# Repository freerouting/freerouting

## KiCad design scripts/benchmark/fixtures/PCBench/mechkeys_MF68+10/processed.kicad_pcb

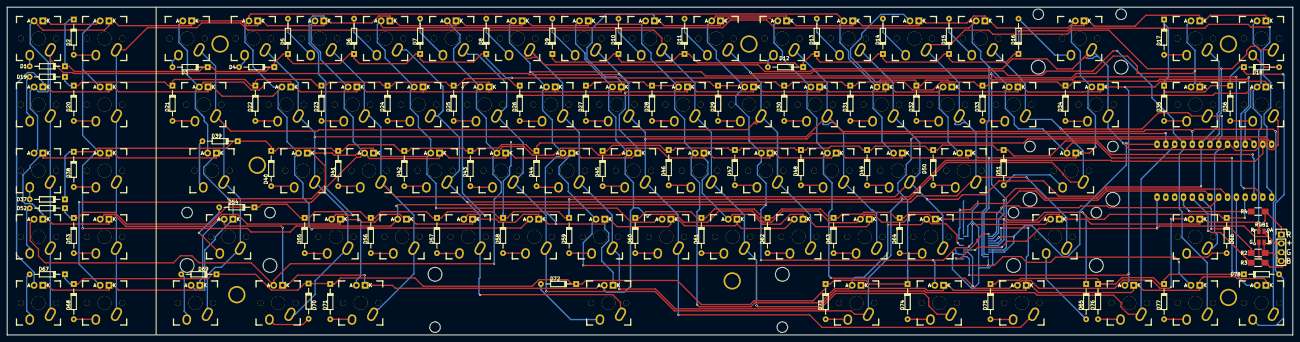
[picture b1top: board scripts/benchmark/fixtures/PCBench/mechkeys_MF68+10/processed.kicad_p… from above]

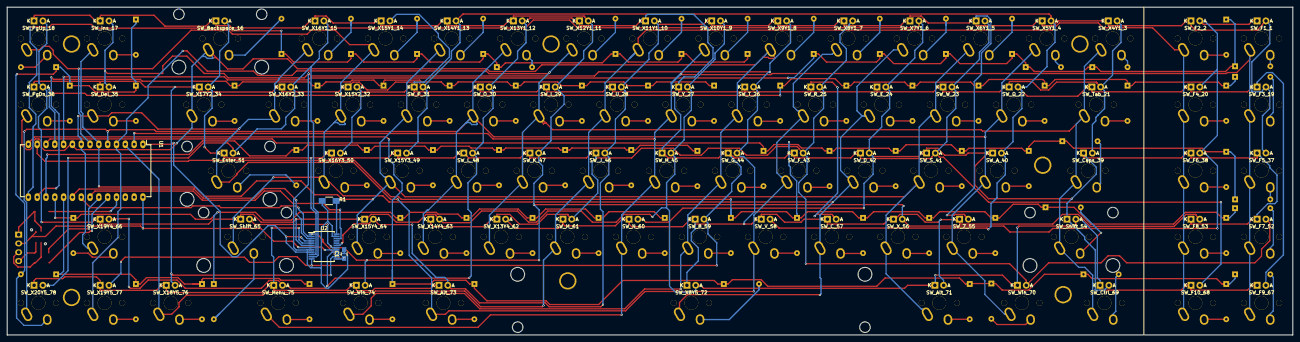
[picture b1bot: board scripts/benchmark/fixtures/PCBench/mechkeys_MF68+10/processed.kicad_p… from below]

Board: 2 copper layers, 370.5 x 94.4 mm, 170 parts (4 on the bottom side), 119 nets.

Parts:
C1: 1µF; C_0805_HandSoldering
CHERRY: MX; CHERRY_PCB_200H_STABILIZER
CHERRY_2, CHERRY_4: MX; CHERRY_PCB_225H_STABILIZER
CHERRY_3: MX; CHERRY_PCB_625H_STABILIZER
CHERRY_5: MX; CHERRY_PCB_275H_STABILIZER
D1, D2, D3, D4, D5, D6, D7, D8, D9, D10, D11, D12, D13, D14, D15, D16, D17, D18, D19, D20, D21, D22, D23, D24, D25, D26, D27, D28, D29, D30, D31, D32, D33, D34, D35, D36, D37, D38, D39, D40, D41, D42, D43, D44, D45, D46, D47, D48, D49, D50, D51, D52, D53, D54, D55, D56, D57, D58, D59, D60, D61, D62, D63, D64, D65, D66, D67, D68, D69, D70, D71, D72, D73, D74, D75, D76, D77, D78: D; Diode_DO-35_SOD27_Horizontal_RM10
GND: MountingHole_5.3mm_M5
R1: 39kΩ; R_1206_HandSoldering
R2: 150Ω; R_1206_HandSoldering
R3, R4: 120Ω; R_1206_HandSoldering
RGB1: Led_RGB_CA; SMP4-RGB
SW_A_40: MX_LED; MXALPS
SW_Alt_71, SW_Alt_73: MX_LED; MXALPS
SW_B_59: MX_LED; MXALPS
SW_Backspace_16: MX_LED; MXALPS
SW_C_57: MX_LED; MXALPS
SW_Caps_39: MX_LED; MXALPS
SW_Ctrl_69: MX_LED; MXALPS
SW_D_42: MX_LED; MXALPS
SW_Del_35: MX_LED; MXALPS
SW_E_24: MX_LED; MXALPS
SW_Enter_51: MX_LED; MXALPS
SW_F1_1, SW_F2_2, SW_F3_19, SW_F4_20, SW_F5_37, SW_F6_38, SW_F7_52, SW_F8_53, SW_F9_67, SW_F10_68: MX_LED; MXALPS
SW_F_43: MX_LED; MXALPS
SW_G_44: MX_LED; MXALPS
SW_H_45: MX_LED; MXALPS
SW_I_29: MX_LED; MXALPS
SW_Ins_17: MX_LED; MXALPS
SW_J_46: MX_LED; MXALPS
SW_K_47: MX_LED; MXALPS
SW_L_48: MX_LED; MXALPS
SW_M_61: MX_LED; MXALPS
SW_Menu_75: MX_LED; MXALPS
SW_N_60: MX_LED; MXALPS
SW_O_30: MX_LED; MXALPS
SW_P_31: MX_LED; MXALPS
SW_PgDn_36: MX_LED; MXALPS
SW_PgUp_18: MX_LED; MXALPS
SW_Q_22: MX_LED; MXALPS
SW_R_25: MX_LED; MXALPS
SW_S_41: MX_LED; MXALPS
SW_Shift_54, SW_Shift_65: MX_LED; MXALPS
SW_T_26: MX_LED; MXALPS
SW_Tab_21: MX_LED; MXALPS
SW_U_28: MX_LED; MXALPS
SW_V_58: MX_LED; MXALPS
SW_W_23: MX_LED; MXALPS
SW_Win_70, SW_Win_74: MX_LED; MXALPS
SW_X4Y1_3, SW_X5Y1_4, SW_X6Y1_5, SW_X7Y1_6, SW_X8Y1_7, SW_X8Y5_72, SW_X9Y1_8, SW_X10Y1_9, SW_X11Y1_10, SW_X12Y1_11, SW_X13Y1_12, SW_X13Y4_62, SW_X14Y1_13, SW_X14Y4_63, SW_X15Y1_14, SW_X15Y2_32, SW_X15Y3_49, SW_X15Y4_64, SW_X16Y1_15, SW_X16Y2_33, SW_X16Y3_50, SW_X17Y2_34, SW_X18Y5_76, SW_X19Y4_66, SW_X19Y5_77, SW_X20Y5_78: MX_LED; MXALPS
SW_X_56: MX_LED; MXALPS
SW_Y_27: MX_LED; MXALPS
SW_Z_55: MX_LED; MXALPS
U1: Teensy_3.2; Teensy3.2
U2: AN32183A; SSOP-24_5.3x8.2mm_Pitch0.65mm

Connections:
+5V: RGB1.1, U1.Vin, U2.7, U2.17
C1: SW_F1_1.SW1, SW_F3_19.SW1, SW_F5_37.SW1, SW_F7_52.SW1, SW_F9_67.SW1, SW_H_45.SW1, SW_Menu_75.SW1, SW_N_60.SW1, SW_X10Y1_9.SW1, SW_Y_27.SW1, U1.0
C2: SW_F2_2.SW1, SW_F4_20.SW1, SW_F6_38.SW1, SW_F8_53.SW1, SW_F10_68.SW1, SW_J_46.SW1, SW_M_61.SW1, SW_U_28.SW1, SW_X11Y1_10.SW1, SW_X18Y5_76.SW1, U1.1
C3: SW_Caps_39.SW1, SW_Ctrl_69.SW1, SW_I_29.SW1, SW_K_47.SW1, SW_Shift_54.SW1, SW_Tab_21.SW1, SW_X4Y1_3.SW1, SW_X12Y1_11.SW1, SW_X13Y4_62.SW1, SW_X19Y5_77.SW1, U1.2
C4: SW_A_40.SW1, SW_L_48.SW1, SW_O_30.SW1, SW_Q_22.SW1, SW_Win_70.SW1, SW_X5Y1_4.SW1, SW_X13Y1_12.SW1, SW_X14Y4_63.SW1, SW_X20Y5_78.SW1, SW_Z_55.SW1, U1.3
C5: SW_Alt_71.SW1, SW_Ins_17.SW1, SW_P_31.SW1, SW_S_41.SW1, SW_W_23.SW1, SW_X6Y1_5.SW1, SW_X14Y1_13.SW1, SW_X15Y3_49.SW1, SW_X15Y4_64.SW1, SW_X_56.SW1, U1.4
C6: SW_C_57.SW1, SW_D_42.SW1, SW_E_24.SW1, SW_PgUp_18.SW1, SW_Shift_65.SW1, SW_X7Y1_6.SW1, SW_X8Y5_72.SW1, SW_X15Y1_14.SW1, SW_X15Y2_32.SW1, SW_X16Y3_50.SW1, U1.5
C7: SW_Alt_73.SW1, SW_Del_35.SW1, SW_Enter_51.SW1, SW_F_43.SW1, SW_R_25.SW1, SW_V_58.SW1, SW_X8Y1_7.SW1, SW_X16Y1_15.SW1, SW_X16Y2_33.SW1, SW_X19Y4_66.SW1, U1.6
C8: SW_B_59.SW1, SW_Backspace_16.SW1, SW_G_44.SW1, SW_PgDn_36.SW1, SW_T_26.SW1, SW_Win_74.SW1, SW_X9Y1_8.SW1, SW_X17Y2_34.SW1, U1.7
GND: C1.2, R1.2, U1.GND0, U2.4, U2.9, U2.15, U2.23
NSRT: U1.20, U2.22
unnamed: C1.1, U2.1, U2.13
unnamed: D1.2, SW_F1_1.SW2
unnamed: D2.2, SW_F2_2.SW2
unnamed: D3.2, SW_X4Y1_3.SW2
unnamed: D4.2, SW_X5Y1_4.SW2
unnamed: D5.2, SW_X6Y1_5.SW2
unnamed: D6.2, SW_X7Y1_6.SW2
unnamed: D7.2, SW_X8Y1_7.SW2
unnamed: D8.2, SW_X9Y1_8.SW2
unnamed: D9.2, SW_X10Y1_9.SW2
unnamed: D10.2, SW_X11Y1_10.SW2
unnamed: D11.2, SW_X12Y1_11.SW2
unnamed: D12.2, SW_X13Y1_12.SW2
unnamed: D13.2, SW_X14Y1_13.SW2
unnamed: D14.2, SW_X15Y1_14.SW2
unnamed: D15.2, SW_X16Y1_15.SW2
unnamed: D16.2, SW_Backspace_16.SW2
unnamed: D17.1, D18.1, D35.1, D36.1, D78.2, SW_X20Y5_78.SW2
unnamed: D17.2, SW_Ins_17.SW2
unnamed: D18.2, SW_PgUp_18.SW2
unnamed: D19.2, SW_F3_19.SW2
unnamed: D20.2, SW_F4_20.SW2
unnamed: D21.2, SW_Tab_21.SW2
unnamed: D22.2, SW_Q_22.SW2
unnamed: D23.2, SW_W_23.SW2
unnamed: D24.2, SW_E_24.SW2
unnamed: D25.2, SW_R_25.SW2
unnamed: D26.2, SW_T_26.SW2
unnamed: D27.2, SW_Y_27.SW2
unnamed: D28.2, SW_U_28.SW2
unnamed: D29.2, SW_I_29.SW2
unnamed: D30.2, SW_O_30.SW2
unnamed: D31.2, SW_P_31.SW2
unnamed: D32.2, SW_X15Y2_32.SW2
unnamed: D33.2, SW_X16Y2_33.SW2
unnamed: D34.2, SW_X17Y2_34.SW2
unnamed: D35.2, SW_Del_35.SW2
unnamed: D36.2, SW_PgDn_36.SW2
unnamed: D37.2, SW_F5_37.SW2
unnamed: D38.2, SW_F6_38.SW2
unnamed: D39.2, SW_Caps_39.SW2
unnamed: D40.2, SW_A_40.SW2
unnamed: D41.2, SW_S_41.SW2
unnamed: D42.2, SW_D_42.SW2
unnamed: D43.2, SW_F_43.SW2
unnamed: D44.2, SW_G_44.SW2
unnamed: D45.2, SW_H_45.SW2
unnamed: D46.2, SW_J_46.SW2
unnamed: D47.2, SW_K_47.SW2
unnamed: D48.2, SW_L_48.SW2
unnamed: D49.2, SW_X15Y3_49.SW2
unnamed: D50.2, SW_X16Y3_50.SW2
unnamed: D51.2, SW_Enter_51.SW2
unnamed: D52.2, SW_F7_52.SW2
unnamed: D53.2, SW_F8_53.SW2
unnamed: D54.2, SW_Shift_54.SW2
unnamed: D55.2, SW_Z_55.SW2
unnamed: D56.2, SW_X_56.SW2
unnamed: D57.2, SW_C_57.SW2
unnamed: D58.2, SW_V_58.SW2
unnamed: D59.2, SW_B_59.SW2
unnamed: D60.2, SW_N_60.SW2
unnamed: D61.2, SW_M_61.SW2
unnamed: D62.2, SW_X13Y4_62.SW2
unnamed: D63.2, SW_X14Y4_63.SW2
unnamed: D64.2, SW_X15Y4_64.SW2
unnamed: D65.2, SW_Shift_65.SW2
unnamed: D66.2, SW_X19Y4_66.SW2
unnamed: D67.2, SW_F9_67.SW2
unnamed: D68.2, SW_F10_68.SW2
unnamed: D69.2, SW_Ctrl_69.SW2
unnamed: D70.2, SW_Win_70.SW2
unnamed: D71.2, SW_Alt_71.SW2
unnamed: D72.2, SW_X8Y5_72.SW2
unnamed: D73.2, SW_Alt_73.SW2
unnamed: D74.2, SW_Win_74.SW2
unnamed: D75.2, SW_Menu_75.SW2
unnamed: D76.2, SW_X18Y5_76.SW2
unnamed: D77.2, SW_X19Y5_77.SW2
unnamed: R1.1, U2.24
unnamed: R2.1, RGB1.4
unnamed: R2.2, U1.21
unnamed: R3.1, RGB1.3
unnamed: R3.2, U1.22
unnamed: R4.1, RGB1.2
unnamed: R4.2, U1.23
R1: D1.1, D2.1, D3.1, D4.1, D5.1, D6.1, D7.1, D8.1, U1.8
R2: D19.1, D20.1, D21.1, D22.1, D23.1, D24.1, D25.1, D26.1, U1.9
R3: D37.1, D38.1, D39.1, D40.1, D41.1, D42.1, D43.1, D44.1, U1.10
R4: D52.1, D53.1, D54.1, D55.1, D56.1, D57.1, D58.1, D59.1, U1.11
R5: D67.1, D68.1, D69.1, D70.1, D71.1, D72.1, D73.1, D74.1, U1.12
R6: D9.1, D10.1, D11.1, D12.1, D13.1, D14.1, D15.1, D16.1, U1.13
R7: D27.1, D28.1, D29.1, D30.1, D31.1, D32.1, D33.1, D34.1, U1.14
R8: D45.1, D46.1, D47.1, D48.1, D49.1, D50.1, D51.1, U1.15
R9: D60.1, D61.1, D62.1, D63.1, D64.1, D65.1, D66.1, U1.16
R10: D75.1, D76.1, D77.1, D78.1, U1.17
SCL: U1.19, U2.2
SDA: U1.18, U2.3
Z1: SW_Alt_73.A, SW_F1_1.A, SW_F2_2.K, SW_F3_19.A, SW_F5_37.A, SW_J_46.A, SW_U_28.A, SW_X4Y1_3.K, SW_X5Y1_4.K, SW_X6Y1_5.K, SW_X7Y1_6.K, SW_X8Y1_7.K, SW_X9Y1_8.K, SW_X10Y1_9.K, SW_X11Y1_10.A, SW_X15Y4_64.A, SW_Z_55.A, U2.19
Z2: SW_Backspace_16.K, SW_F1_1.K, SW_F2_2.A, SW_F4_20.A, SW_F6_38.A, SW_I_29.A, SW_Ins_17.K, SW_K_47.A, SW_PgUp_18.K, SW_Shift_65.A, SW_Win_74.A, SW_X12Y1_11.A, SW_X13Y1_12.K, SW_X14Y1_13.K, SW_X15Y1_14.K, SW_X16Y1_15.K, SW_X_56.A, U2.18
Z3: SW_C_57.A, SW_Caps_39.A, SW_E_24.K, SW_L_48.A, SW_Menu_75.A, SW_O_30.A, SW_Q_22.K, SW_R_25.K, SW_T_26.K, SW_Tab_21.A, SW_W_23.K, SW_X4Y1_3.A, SW_X11Y1_10.K, SW_X12Y1_11.K, SW_X13Y1_12.A, SW_X19Y4_66.A, SW_Y_27.K, U2.16
Z4: SW_A_40.A, SW_Del_35.K, SW_F3_19.K, SW_F4_20.K, SW_F9_67.A, SW_P_31.A, SW_PgDn_36.K, SW_Q_22.A, SW_Tab_21.K, SW_V_58.A, SW_X5Y1_4.A, SW_X14Y1_13.A, SW_X15Y2_32.K, SW_X15Y3_49.A, SW_X16Y2_33.K, SW_X17Y2_34.K, SW_X18Y5_76.A, U2.14
Z5: SW_B_59.A, SW_D_42.K, SW_F10_68.A, SW_F_43.K, SW_G_44.K, SW_H_45.K, SW_I_29.K, SW_O_30.K, SW_P_31.K, SW_S_41.A, SW_U_28.K, SW_W_23.A, SW_X6Y1_5.A, SW_X15Y1_14.A, SW_X15Y2_32.A, SW_X16Y3_50.A, SW_X19Y5_77.A, U2.12
Z6: SW_A_40.K, SW_Caps_39.K, SW_Ctrl_69.A, SW_D_42.A, SW_E_24.A, SW_Enter_51.A, SW_F5_37.K, SW_F6_38.K, SW_F7_52.K, SW_F8_53.K, SW_N_60.A, SW_S_41.K, SW_Shift_54.K, SW_X7Y1_6.A, SW_X16Y1_15.A, SW_X16Y2_33.A, SW_X20Y5_78.A, U2.11
Z7: SW_Backspace_16.A, SW_Enter_51.K, SW_F7_52.A, SW_F_43.A, SW_J_46.K, SW_K_47.K, SW_L_48.K, SW_M_61.A, SW_R_25.A, SW_Win_70.A, SW_X8Y1_7.A, SW_X13Y4_62.K, SW_X14Y4_63.K, SW_X15Y3_49.K, SW_X16Y3_50.K, SW_X17Y2_34.A, U2.10
Z8: SW_Alt_71.A, SW_B_59.K, SW_C_57.K, SW_Del_35.A, SW_F8_53.A, SW_G_44.A, SW_Ins_17.A, SW_M_61.K, SW_N_60.K, SW_T_26.A, SW_V_58.K, SW_X8Y5_72.K, SW_X9Y1_8.A, SW_X13Y4_62.A, SW_X_56.K, SW_Z_55.K, U2.8
Z9: SW_Alt_71.K, SW_Ctrl_69.K, SW_F9_67.K, SW_F10_68.K, SW_H_45.A, SW_PgDn_36.A, SW_PgUp_18.A, SW_Shift_54.A, SW_Shift_65.K, SW_Win_70.K, SW_X8Y5_72.A, SW_X10Y1_9.A, SW_X14Y4_63.A, SW_X15Y4_64.K, SW_X19Y4_66.K, SW_Y_27.A, U2.6
Z10: SW_Alt_73.K, SW_Menu_75.K, SW_Win_74.K, SW_X18Y5_76.K, SW_X19Y5_77.K, SW_X20Y5_78.K, U2.5

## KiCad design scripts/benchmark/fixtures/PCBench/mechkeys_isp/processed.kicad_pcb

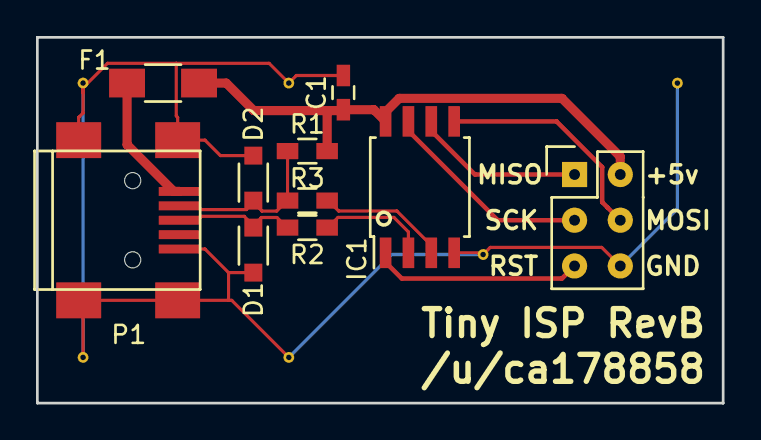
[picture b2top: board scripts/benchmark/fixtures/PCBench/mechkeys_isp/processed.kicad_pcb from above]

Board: 2 copper layers, 38.1 x 20.3 mm, 10 parts (0 on the bottom side), 11 nets.

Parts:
C1: 0.1µF; C_0603_HandSoldering
D1, D2: 3.6v; SOD-323_HandSoldering
F1: F_Small; C_1206_HandSoldering
IC1: ATTINY45-S; SOIJ-8_5.3x5.3mm_Pitch1.27mm
P1: USB_OTG; USB_Mini-B
P2: CONN_02X03; Pin_Header_Straight_2x03
R1: 1.7kΩ; R_0603_HandSoldering
R2, R3: 68Ω; R_0603_HandSoldering

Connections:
+5V: C1.1, F1.1, IC1.8, P2.2, R1.1
D+: D1.1, P1.3, R2.2
D-: D2.1, P1.2, R1.2, R3.2
GND: C1.2, D1.2, D2.2, IC1.4, P1.5, P1.6, P2.6
MISO: IC1.6, P2.1
MOSI: IC1.5, P2.4
unnamed: F1.2, P1.1
unnamed: IC1.2, R2.1
unnamed: IC1.3, R3.1
RST: IC1.1, P2.5
SCK: IC1.7, P2.3
